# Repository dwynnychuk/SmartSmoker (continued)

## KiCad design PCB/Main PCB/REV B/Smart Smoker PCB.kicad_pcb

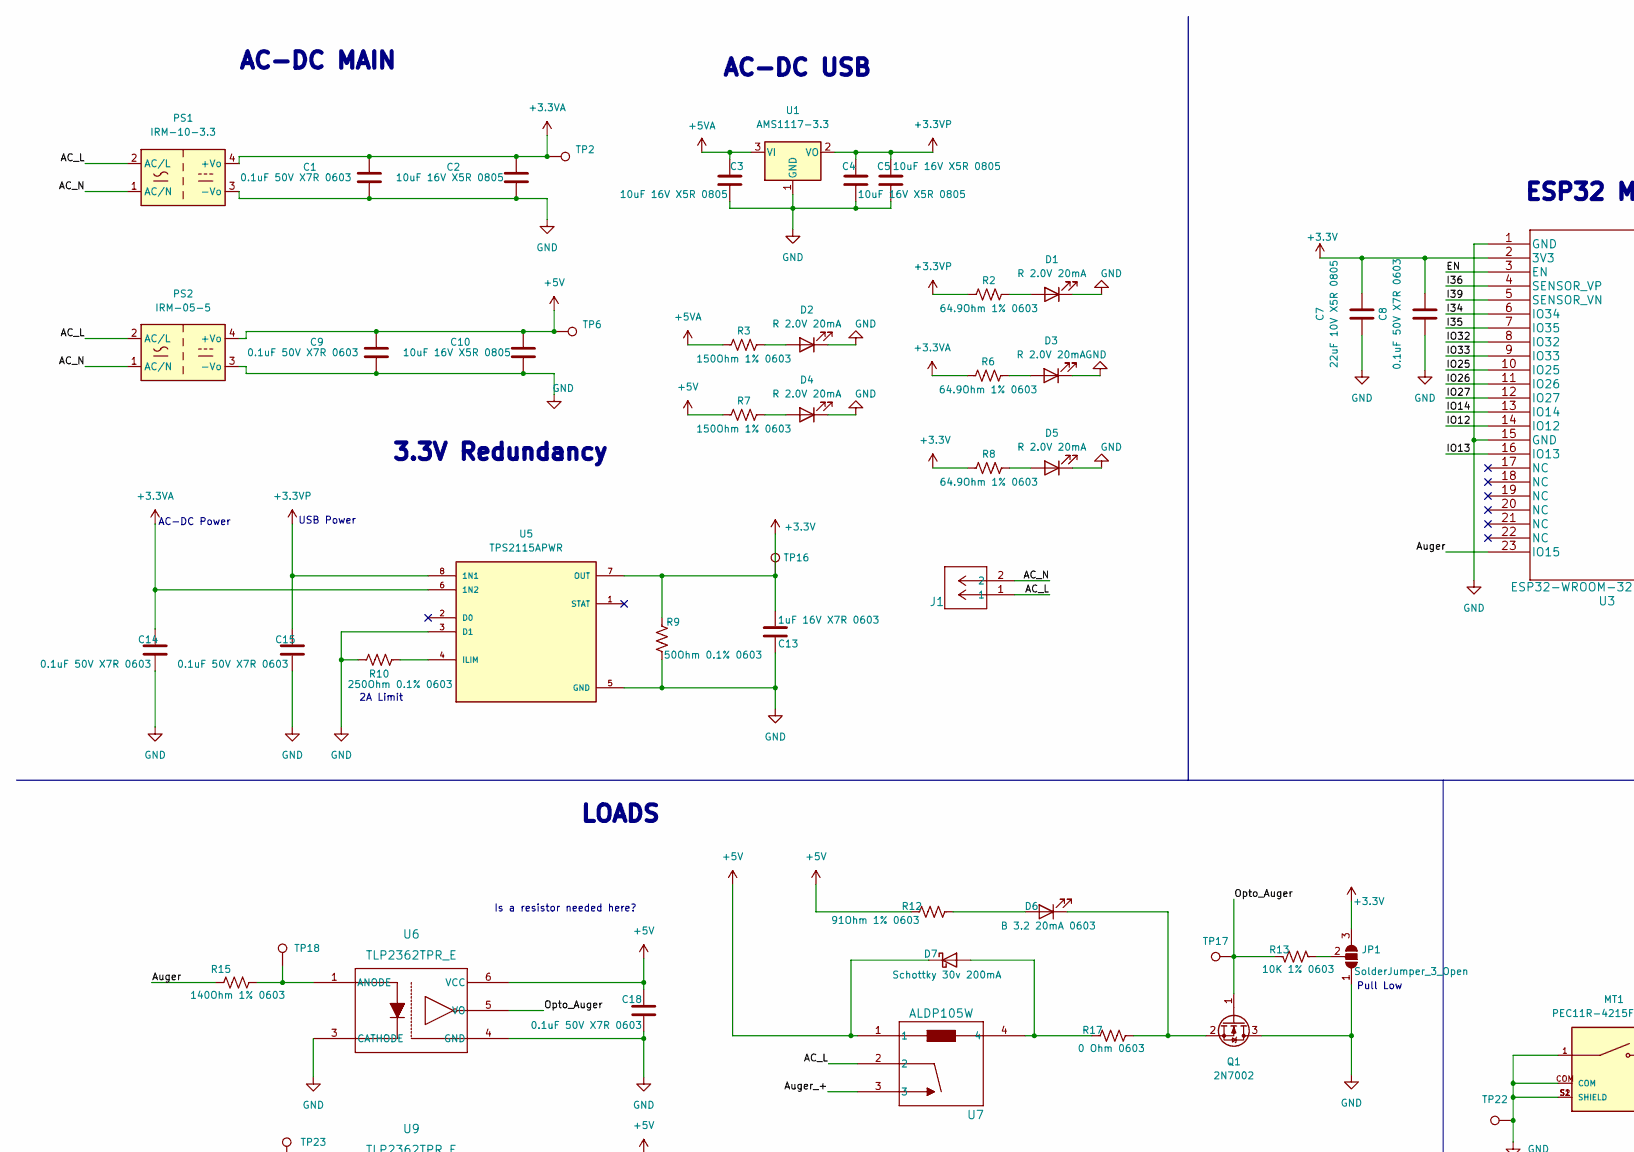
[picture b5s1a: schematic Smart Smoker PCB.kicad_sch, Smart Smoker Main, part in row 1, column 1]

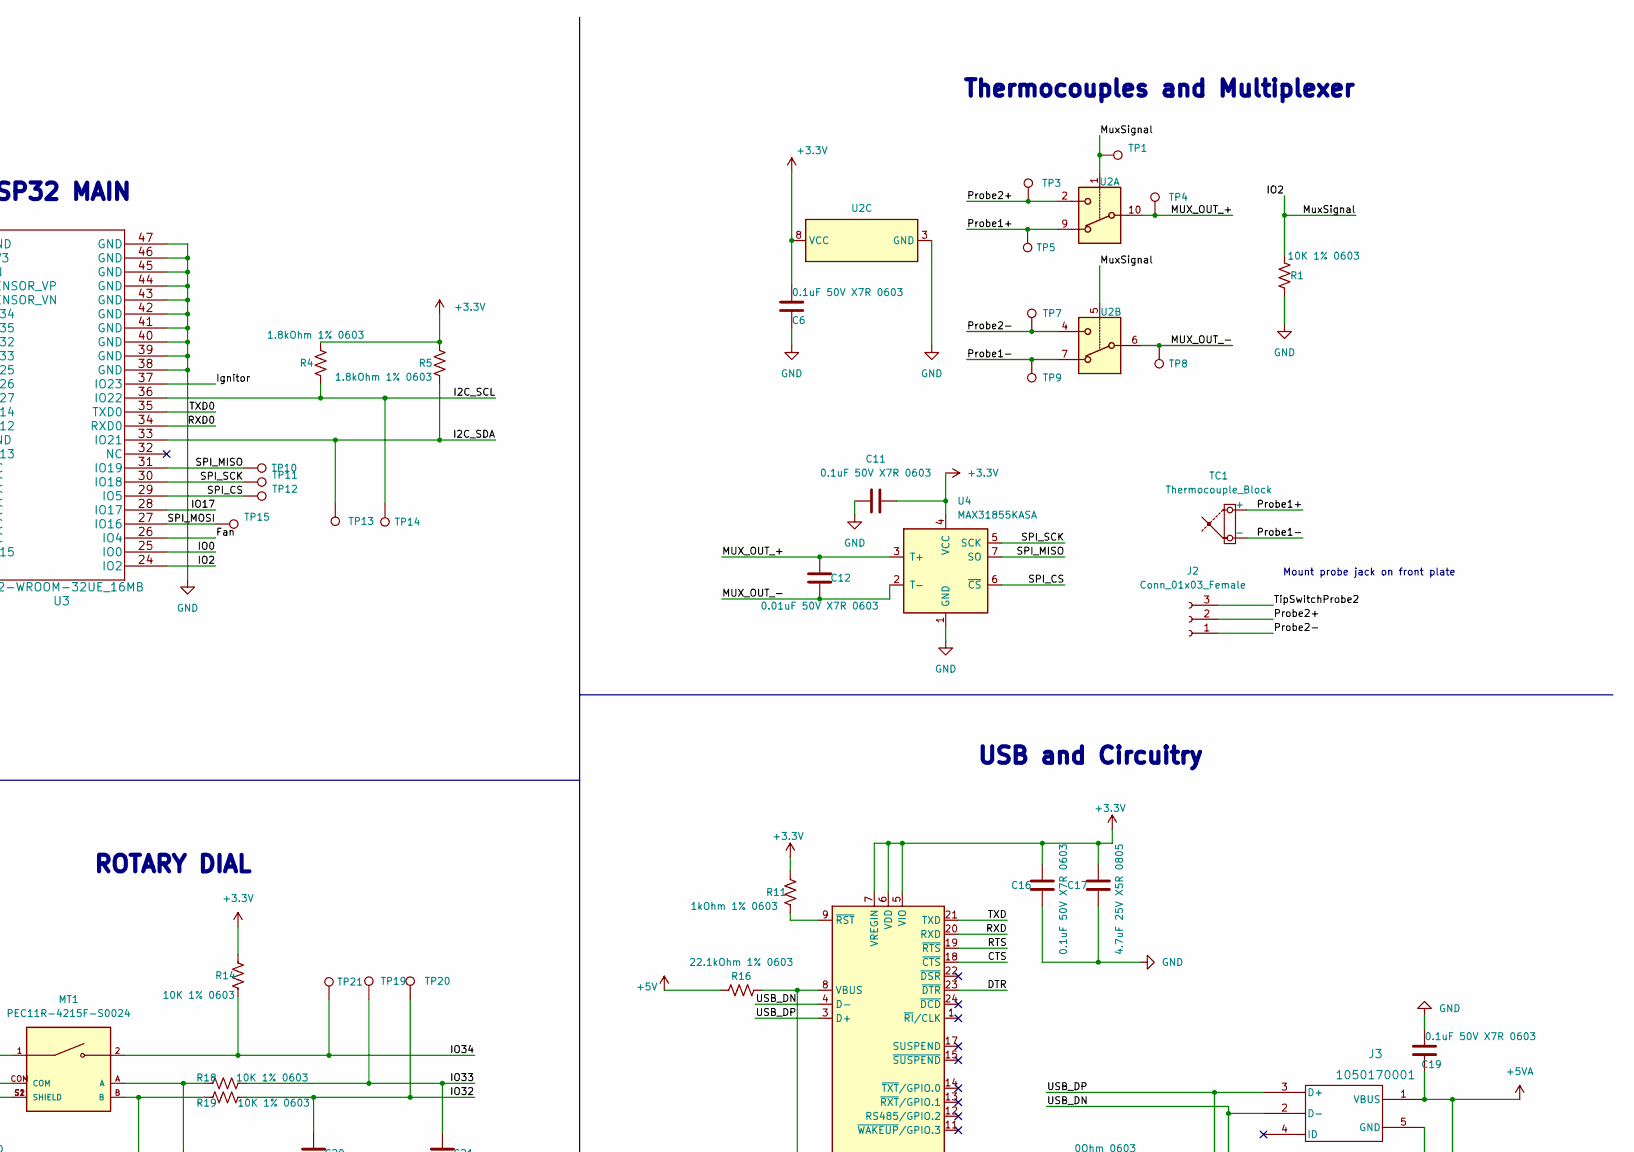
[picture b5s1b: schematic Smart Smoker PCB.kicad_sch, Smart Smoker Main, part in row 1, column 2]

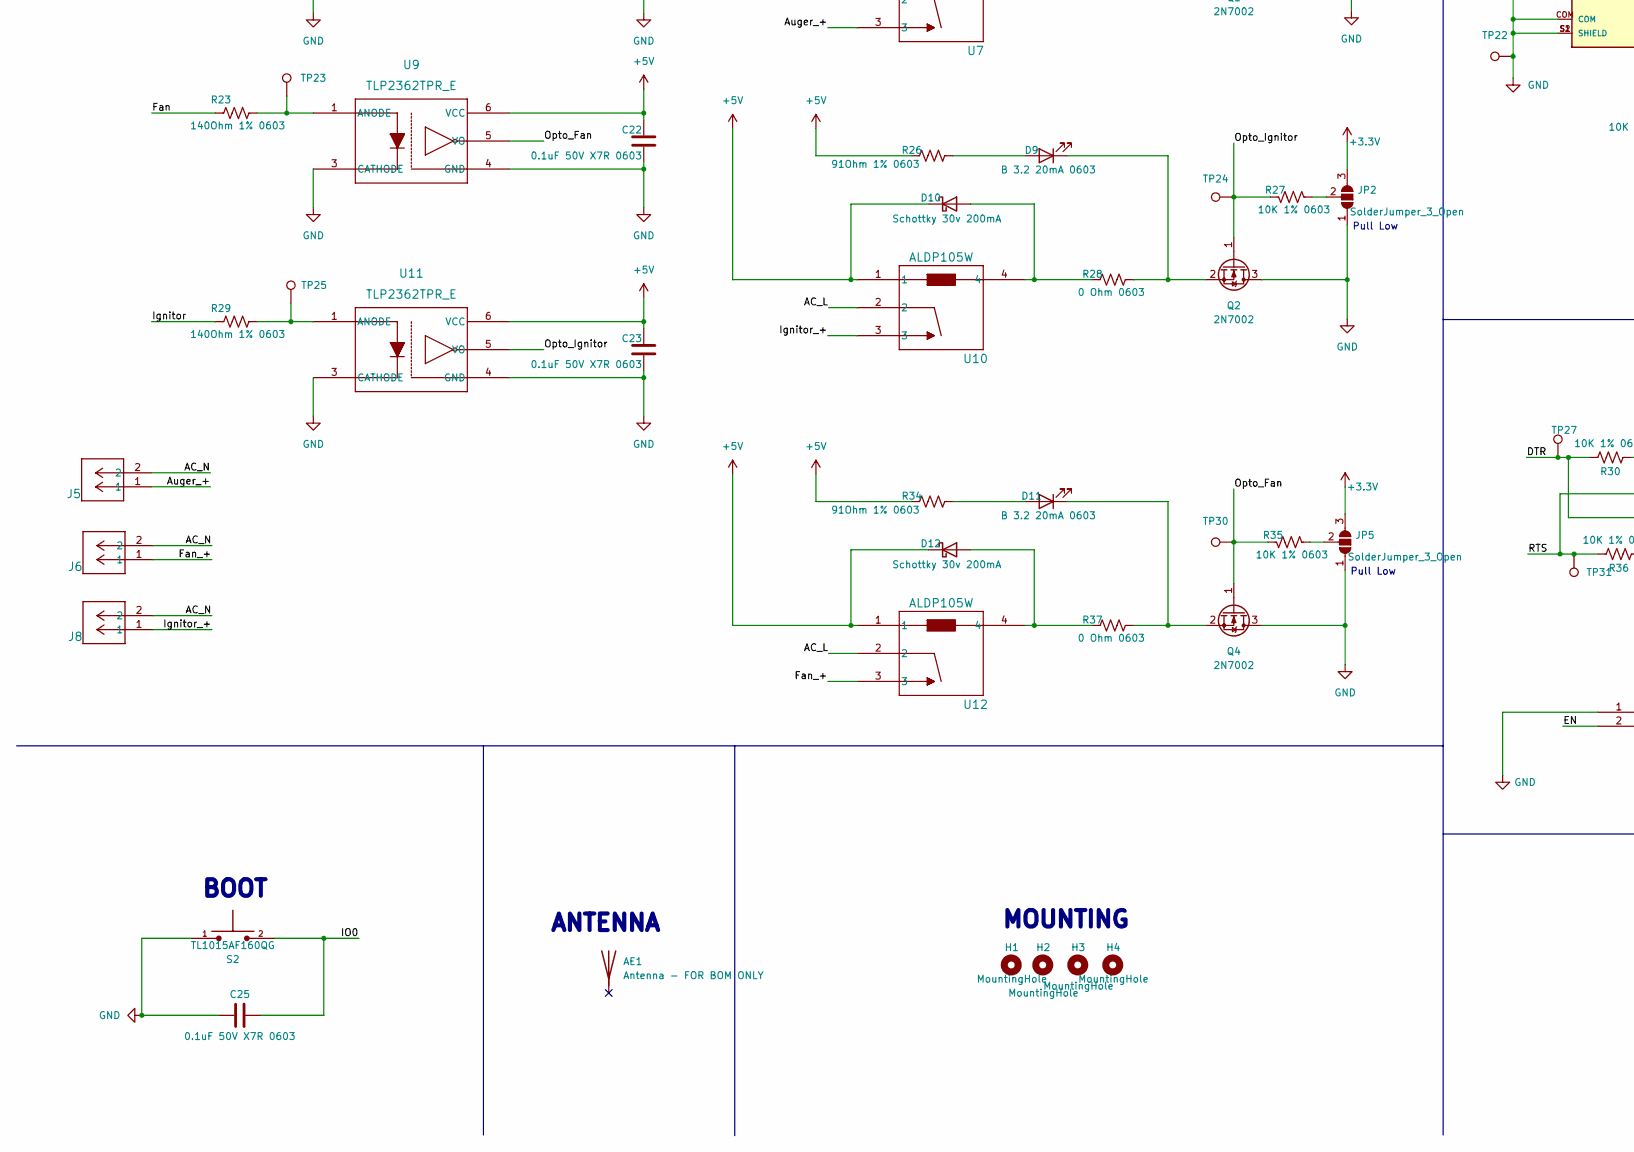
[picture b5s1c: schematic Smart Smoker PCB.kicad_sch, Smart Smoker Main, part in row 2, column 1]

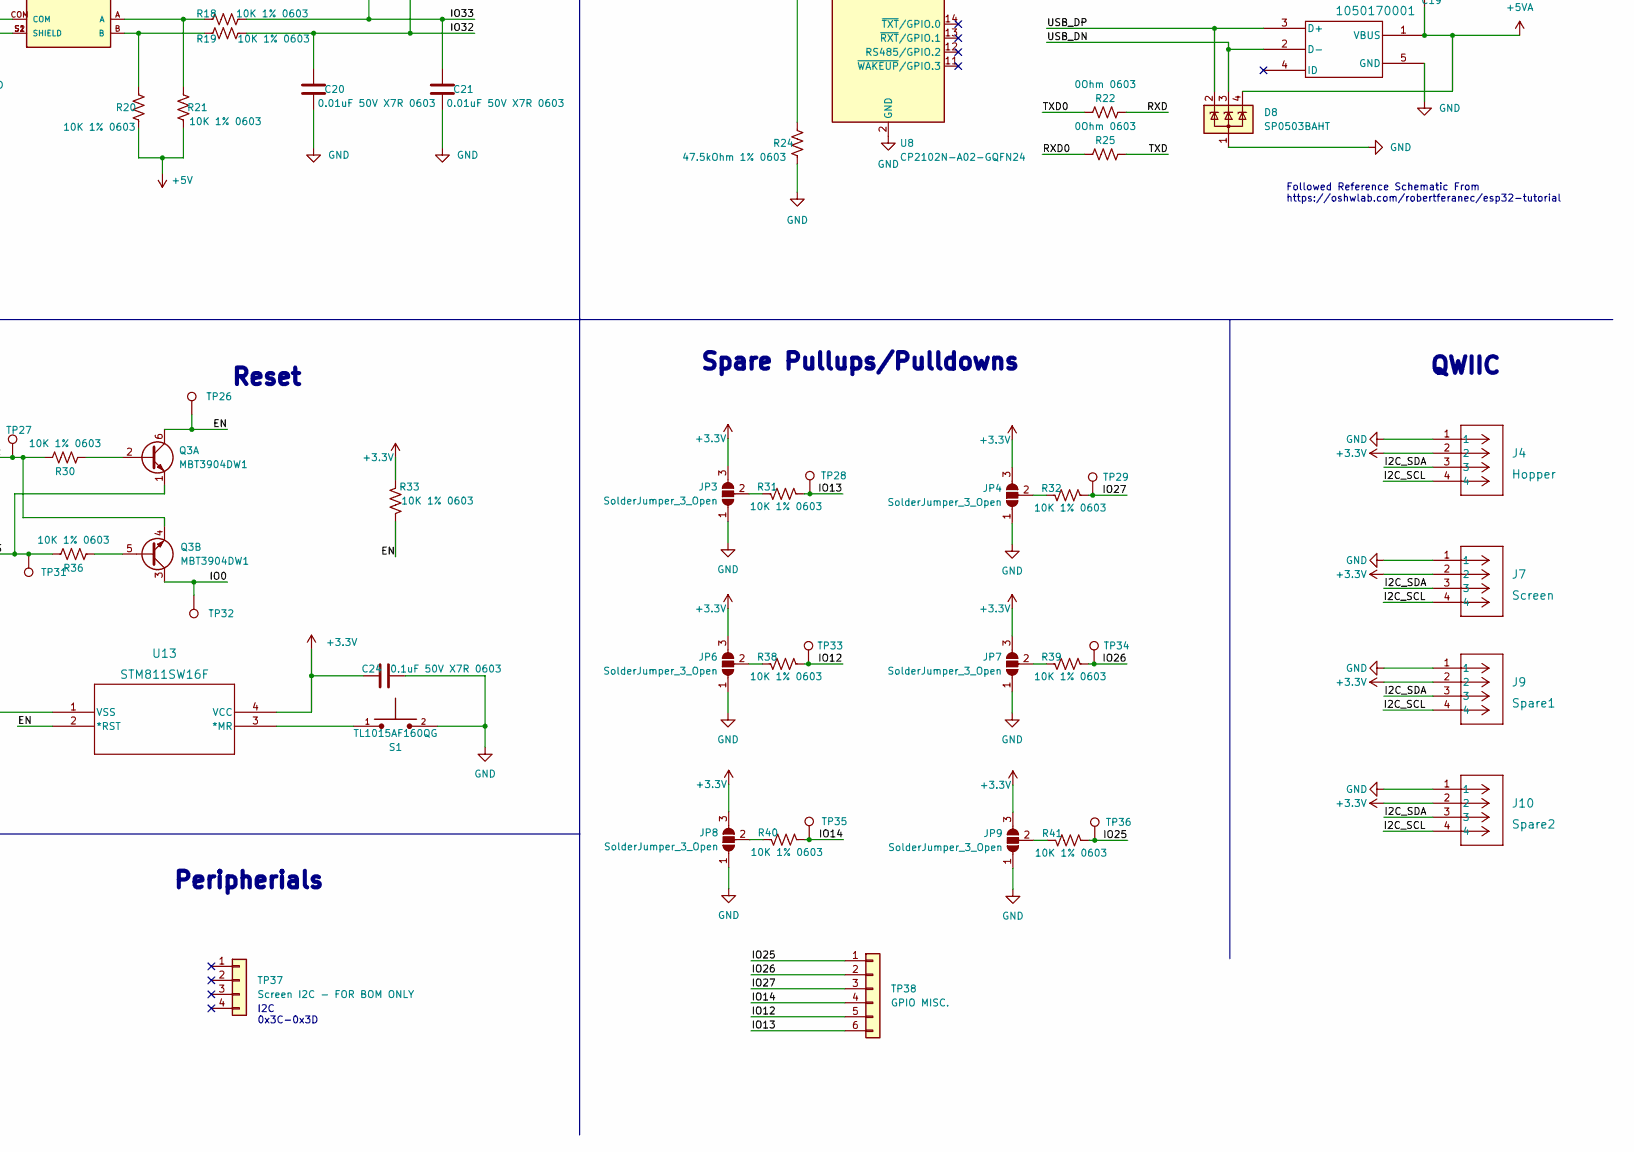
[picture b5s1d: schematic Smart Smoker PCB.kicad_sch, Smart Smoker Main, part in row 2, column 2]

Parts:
AE1: Antenna - FOR BOM ONLY; KiCad-Logo2_5mm_SilkScreen; Manufacturer Part Number W3921B0100
C1, C6, C8, C9, C11, C14, C15, C16, C18, C19, C22, C23, C24, C25: 0.1uF 50V X7R 0603; C_0603_1608Metric; Manufacturer Part Number CL10B104KB8NNWC
C2, C3, C4, C5, C10: 10uF 16V X5R 0805; C_0805_2012Metric; Manufacturer Part Number CL21A106KOQNNNE
C7: 22uF 10V X5R 0805; C_0805_2012Metric; Manufacturer Part Number CL21A226MPQNNNE
C12, C20, C21: 0.01uF 50V X7R 0603; C_0603_1608Metric; Manufacturer Part Number CL10B103KB8NNNC
C13: 1uF 16V X7R 0603; C_0603_1608Metric; Manufacturer Part Number CC0603KRX7R7BB105
C17: 4.7uF 25V X5R 0805; C_0805_2012Metric; Manufacturer Part Number CL21A475KAQNNNE
D1, D2, D3, D4, D5: R 2.0V 20mA; LED_0603_1608Metric; Manufacturer Part Number LO Q976-PS-25-0-20-R18
D6, D9, D11: B 3.2 20mA 0603; LED_0603_1608Metric; Manufacturer Part Number 150060BS75000
D7, D10, D12: Schottky 30v 200mA; RB521S30T1G-M; Manufacturer Part Number RB521S30T1G
D8: SP0503BAHT; SOT-143; Manufacturer Part Number SP0503BAHTG
H1, H2, H3, H4: MountingHole; MountingHole_3.2mm_M3_DIN965_Pad
J1, J5, J6, J8: 393570002; CONN_393570002_MOL; Manufacturer Part Number 393570002
J2: Conn_01x03_Female; PinHeader_1x03_P2.54mm_Vertical; Manufacturer Part Number MJ-3502
J3: 1050170001; USB_Micro-B_Molex-105017-0001; Manufacturer Part Number 1050170001
J4: Hopper; PRT-14417; Manufacturer Part Number PRT-14417
J7: Screen; PRT-14417; Manufacturer Part Number PRT-14417
J9: Spare1; PRT-14417; Manufacturer Part Number PRT-14417
J10: Spare2; PRT-14417; Manufacturer Part Number PRT-14417
JP1, JP2, JP3, JP4, JP5, JP6, JP7, JP8, JP9: SolderJumper_3_Open; SolderJumper-3_P1.3mm_Open_RoundedPad1.0x1.5mm
MT1: PEC11R-4215F-S0024; XDCR_PEC11R-4215F-S0024; Manufacturer Part Number PEC11R-4220K-S0024
PS1: IRM-10-3.3; Converter_ACDC_MeanWell_IRM-10-xx_THT; Manufacturer Part Number IRM-10-3.3
PS2: IRM-05-5; Converter_ACDC_MeanWell_IRM-05-xx_THT
Q1, Q2, Q4: 2N7002; SOT-23; Manufacturer Part Number 1727-4789-1-ND
Q3: MBT3904DW1; SOT-363_SC-70-6
R1, R13, R14, R18, R19, R20, R21, R27, R30, R31, R32, R33, R35, R36, R38, R39, R40, R41: 10K 1% 0603; R_0603_1608Metric; Manufacturer Part Number RNCP0603FTD10K0
R2, R6, R8: 64.9Ohm 1% 0603; R_0603_1608Metric; Manufacturer Part Number RC0603FR-0764R9L
R3, R7: 150Ohm 1% 0603; R_0603_1608Metric; Manufacturer Part Number RC0603FR-07150RL
R4, R5: 1.8kOhm 1% 0603; R_0603_1608Metric; Manufacturer Part Number CRGCQ0603F1K8
R9: 50Ohm 0.1% 0603; R_0603_1608Metric; Manufacturer Part Number RT0603BRE0750RL
R10: 250Ohm 0.1% 0603; R_0603_1608Metric; Manufacturer Part Number RT0603BRE07250RL
R11: 1kOhm 1% 0603; R_0603_1608Metric; Manufacturer Part Number RNCP0603FTD1K00
R12, R26, R34: 91Ohm 1% 0603; R_0603_1608Metric; Manufacturer Part Number RC0603FR-0791RL
R15, R23, R29: 140Ohm 1% 0603; R_0603_1608Metric; Manufacturer Part Number RC0603FR-07140RL
R16: 22.1kOhm 1% 0603; R_0603_1608Metric; Manufacturer Part Number RC0603FR-0722K1L
R17, R28, R37: 0 Ohm 0603; R_0603_1608Metric; Manufacturer Part Number RC0603JR-070RL
R22, R25: 0Ohm 0603; R_0603_1608Metric; Manufacturer Part Number RMCF0603ZT0R00
R24: 47.5kOhm 1% 0603; R_0603_1608Metric; Manufacturer Part Number RC0603FR-0747K5L
S1, S2: TL1015AF160QG; SW_TL1015AF160QG; PARTREV F
TC1: Thermocouple_Block; K-TypeAdapter; Manufacturer Part Number XE-1139-001
TP1, TP2, TP3, TP4, TP5, TP6, TP7, TP8, TP9, TP10, TP11, TP12, TP13, TP14, TP15, TP16, TP17, TP18, TP19, TP20, TP21, TP22, TP23, TP24, TP25, TP26, TP27, TP28, TP29, TP30, TP31, TP32, TP33, TP34, TP35, TP36: TP; TestPoint_Pad_D1.0mm
TP37: Screen I2C - FOR BOM ONLY; PinHeader_1x04_P2.54mm_Vertical; Manufacturer Part Number 938
TP38: GPIO MISC.; PinHeader_1x06_P2.54mm_Vertical
U1: AMS1117-3.3; TO-252-2; Manufacturer Part Number AMS1117CD-3.3
U2: TS5A23159DGS; VSSOP-10_3x3mm_P0.5mm; Manufacturer Part Number TS5A23159DGSR
U3: ESP32-WROOM-32UE_16MB; ESP32-WROOM-32UE 16MB; Manufacturer Part Number ESP32-WROOM-32UE-N4
U4: MAX31855KASA; SOIC-8_3.9x4.9mm_P1.27mm; Manufacturer Part Number MAX31855KASA+T
U5: TPS2115APWR; PW8-M; Manufacturer Part Number TPS2115APWR
U6, U9, U11: TLP2362TPR_E; TLP2362; Manufacturer Part Number TLP2362(TPR,E
U7, U10, U12: ALDP105W; PAN_ALD_PAN; Manufacturer Part Number ALDP105W
U8: CP2102N-A02-GQFN24; QFN-24-1EP_4x4mm_P0.5mm_EP2.6x2.6mm; Manufacturer Part Number CP2102N-A02-GQFN24
U13: STM811SW16F; Manufacturer Part Number STM811SW16F

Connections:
+3.3V: C6.2, C7.2, C8.2, C11.1, C13.1, C16.2, C17.2, C24.2, J4.2, J7.2, J9.2, J10.2, JP1.3 (B), JP2.3 (B), JP3.3 (B), JP4.3 (B), JP5.3 (B), JP6.3 (B), JP7.3 (B), JP8.3 (B), JP9.3 (B), R4.2, R5.2, R8.1, R9.2, R11.2, R14.2, R33.2, TP16.1, U2.8 (VCC), U3.2 (3V3), U4.4 (VCC), U5.7 (OUT), U8.5 (VIO), U8.6 (VDD), U8.7 (VREGIN), U13.4 (VCC)
+3.3VA: C1.2, C2.1, C14.2, PS1.4 (+Vo), R6.1, TP2.1, U5.6 (1N2)
+3.3VP: C4.1, C5.1, C15.2, R2.1, U1.2 (VO), U5.8 (1N1)
+5V: C9.2, C10.1, C18.1, C22.1, C23.1, D7.1 (K), D10.1 (K), D12.1 (K), PS2.4 (+Vo), R7.1, R12.1, R16.1, R20.1, R21.1, R26.1, R34.1, TP6.1, U6.6 (VCC), U7.1, U9.6 (VCC), U10.1, U11.6 (VCC), U12.1
+5VA: C3.1, C19.1, D8.4 (K), J3.1 (VBUS), R3.1, U1.3 (VI)
/AC_L: J1.1, PS1.2 (AC/L), PS2.2 (AC/L), U7.2, U10.2, U12.2
/AC_N: J1.2, J5.2, J6.2, J8.2, PS1.1 (AC/N), PS2.1 (AC/N)
/Auger: R15.1, U3.23 (IO15)
/Auger_+: J5.1, U7.3
/CTS: U8.18 (~CTS)
/DTR: Q3.4 (E2), R30.1, TP27.1, U8.23 (~DTR)
/EN: Q3.6 (C1), R33.1, TP26.1, U3.3 (EN), U13.2 (*RST)
/Fan: R23.1, U3.26 (IO4)
/Fan_+: J6.1, U12.3
/I2C_SCL: J4.4, J7.4, J9.4, J10.4, R4.1, TP14.1, U3.36 (IO22)
/I2C_SDA: J4.3, J7.3, J9.3, J10.3, R5.1, TP13.1, U3.33 (IO21)
/I34: U3.6 (IO34)
/I35: U3.7 (IO35)
/I36: U3.4 (SENSOR_VP)
/I39: U3.5 (SENSOR_VN)
/IO0: C25.1, Q3.3 (C2), S2.2, TP32.1, U3.25 (IO0)
/IO2: R1.1, TP1.1, U2.1, U2.5, U3.24 (IO2)
/IO12: R38.1, TP33.1, TP38.5, U3.14 (IO12)
/IO13: R31.1, TP28.1, TP38.6, U3.16 (IO13)
/IO14: R40.1, TP35.1, TP38.4, U3.13 (IO14)
/IO17: U3.28 (IO17)
/IO25: R41.1, TP36.1, TP38.1, U3.10 (IO25)
/IO26: R39.1, TP34.1, TP38.2, U3.11 (IO26)
/IO27: R32.1, TP29.1, TP38.3, U3.12 (IO27)
/IO32: C20.1, R19.2, TP20.1, U3.8 (IO32)
/IO33: C21.1, R18.2, TP19.1, U3.9 (IO33)
/IO34: MT1.2, R14.1, TP21.1
/Ignitor: R29.1, U3.37 (IO23)
/Ignitor_+: J8.1, U10.3
/MUX_OUT_+: C12.1, TP4.1, U2.10, U4.3 (T+)
/MUX_OUT_-: C12.2, TP8.1, U2.6, U4.2 (T-)
/Opto_Auger: Q1.1 (G), R13.2, TP17.1, U6.5 (VO)
/Opto_Fan: Q4.1 (G), R35.2, TP30.1, U9.5 (VO)
/Opto_Ignitor: Q2.1 (G), R27.2, TP24.1, U11.5 (VO)
/Probe1+: TC1.1 (+), TP5.1, U2.9
/Probe1-: TC1.2 (-), TP9.1, U2.7
/Probe2+: J2.2, TP3.1, U2.2
/Probe2-: J2.1, TP7.1, U2.4
/RTS: Q3.1 (E1), R36.1, TP31.1, U8.19 (~RTS)
/RXD: R22.2, U8.20 (RXD)
/RXD0: R25.1, U3.34 (RXD0)
/SPI_CS: TP12.1, U3.29 (IO5), U4.6 (~CS)
/SPI_MISO: TP10.1, U3.31 (IO19), U4.7 (SO)
/SPI_MOSI: TP15.1, U3.27 (IO16)
/SPI_SCK: TP11.1, U3.30 (IO18), U4.5 (SCK)
/TXD: R25.2, U8.21 (TXD)
/TXD0: R22.1, U3.35 (TXD0)
/TipSwitchProbe2: J2.3
/USB_DN: D8.3 (K), J3.2 (D-), U8.4 (D-)
/USB_DP: D8.2 (K), J3.3 (D+), U8.3 (D+)
GND: C1.1, C2.2, C3.2, C4.2, C5.2, C6.1, C7.1, C8.1, C9.1, C10.2, C11.2, C13.2, C14.1, C15.1, C16.1, C17.1, C18.2, C19.2, C20.2, C21.2, C22.2, C23.2, C24.1, C25.2, D1.1 (K), D2.1 (K), D3.1 (K), D4.1 (K), D5.1 (K), D8.1 (A), J3.5 (GND), J4.1, J7.1, J9.1, J10.1, JP1.1 (A), JP2.1 (A), JP3.1 (A), JP4.1 (A), JP5.1 (A), JP6.1 (A), JP7.1 (A), JP8.1 (A), JP9.1 (A), MT1.1, MT1.COM, MT1.S1 (SHIELD), MT1.S2 (SHIELD), PS1.3 (-Vo), PS2.3 (-Vo), Q1.3 (D), Q2.3 (D), Q4.3 (D), R1.2, R9.1, R10.2, R24.1, S1.2, S2.1, TP22.1, U1.1 (GND), U2.3 (GND), U3.1 (GND), U3.15 (GND), U3.38 (GND), U3.39 (GND), U3.40 (GND), U3.41 (GND), U3.42 (GND), U3.43 (GND), U3.44 (GND), U3.45 (GND), U3.46 (GND), U3.47 (GND), U4.1 (GND), U5.3 (D1), U5.5 (GND), U6.3 (CATHODE), U6.4 (GND), U8.2 (GND), U8.25 (GND), U9.3 (CATHODE), U9.4 (GND), U11.3 (CATHODE), U11.4 (GND), U13.1 (VSS)
unnamed: D1.2 (A), R2.2
unnamed: D2.2 (A), R3.2
unnamed: D3.2 (A), R6.2
unnamed: D4.2 (A), R7.2
unnamed: D5.2 (A), R8.2
unnamed: D6.1 (K), Q1.2 (S), R17.2
unnamed: D6.2 (A), R12.2
unnamed: D7.2 (A), R17.1, U7.4
unnamed: D9.1 (K), Q2.2 (S), R28.2
unnamed: D9.2 (A), R26.2
unnamed: D10.2 (A), R28.1, U10.4
unnamed: D11.1 (K), Q4.2 (S), R37.2
unnamed: D11.2 (A), R34.2
unnamed: D12.2 (A), R37.1, U12.4
unnamed: JP1.2 (C), R13.1
unnamed: JP2.2 (C), R27.1
unnamed: JP3.2 (C), R31.2
unnamed: JP4.2 (C), R32.2
unnamed: JP5.2 (C), R35.1
unnamed: JP6.2 (C), R38.2
unnamed: JP7.2 (C), R39.2
unnamed: JP8.2 (C), R40.2
unnamed: JP9.2 (C), R41.2
unnamed: MT1.A, R18.1, R21.2
unnamed: MT1.B, R19.1, R20.2
unnamed: Q3.2 (B1), R30.2
unnamed: Q3.5 (B2), R36.2
unnamed: R10.1, U5.4 (ILIM)
unnamed: R11.1, U8.9 (~RST)
unnamed: R15.2, TP18.1, U6.1 (ANODE)
unnamed: R16.2, R24.2, U8.8 (VBUS)
unnamed: R23.2, TP23.1, U9.1 (ANODE)
unnamed: R29.2, TP25.1, U11.1 (ANODE)
unnamed: S1.1, U13.3 (*MR)

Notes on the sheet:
Peripherials
MOUNTING
Reset
2A Limit
Pull Low
AC-DC USB
BOOT
USB and Circuitry
USB Power
Is a resistor needed here?
LOADS
I2C 0x3C-0x3D
Spare Pullups/Pulldowns
Thermocouples and Multiplexer
Mount probe jack on front plate
Followed Reference Schematic From https://oshwlab.com/robertferanec/esp32-tutorial
QWIIC
AC-DC Power
ANTENNA
ESP32 MAIN
ROTARY DIAL
3.3V Redundancy
AC-DC MAIN

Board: 4 copper layers, 161 parts (0 on the bottom side), 83 nets, no tracks yet.

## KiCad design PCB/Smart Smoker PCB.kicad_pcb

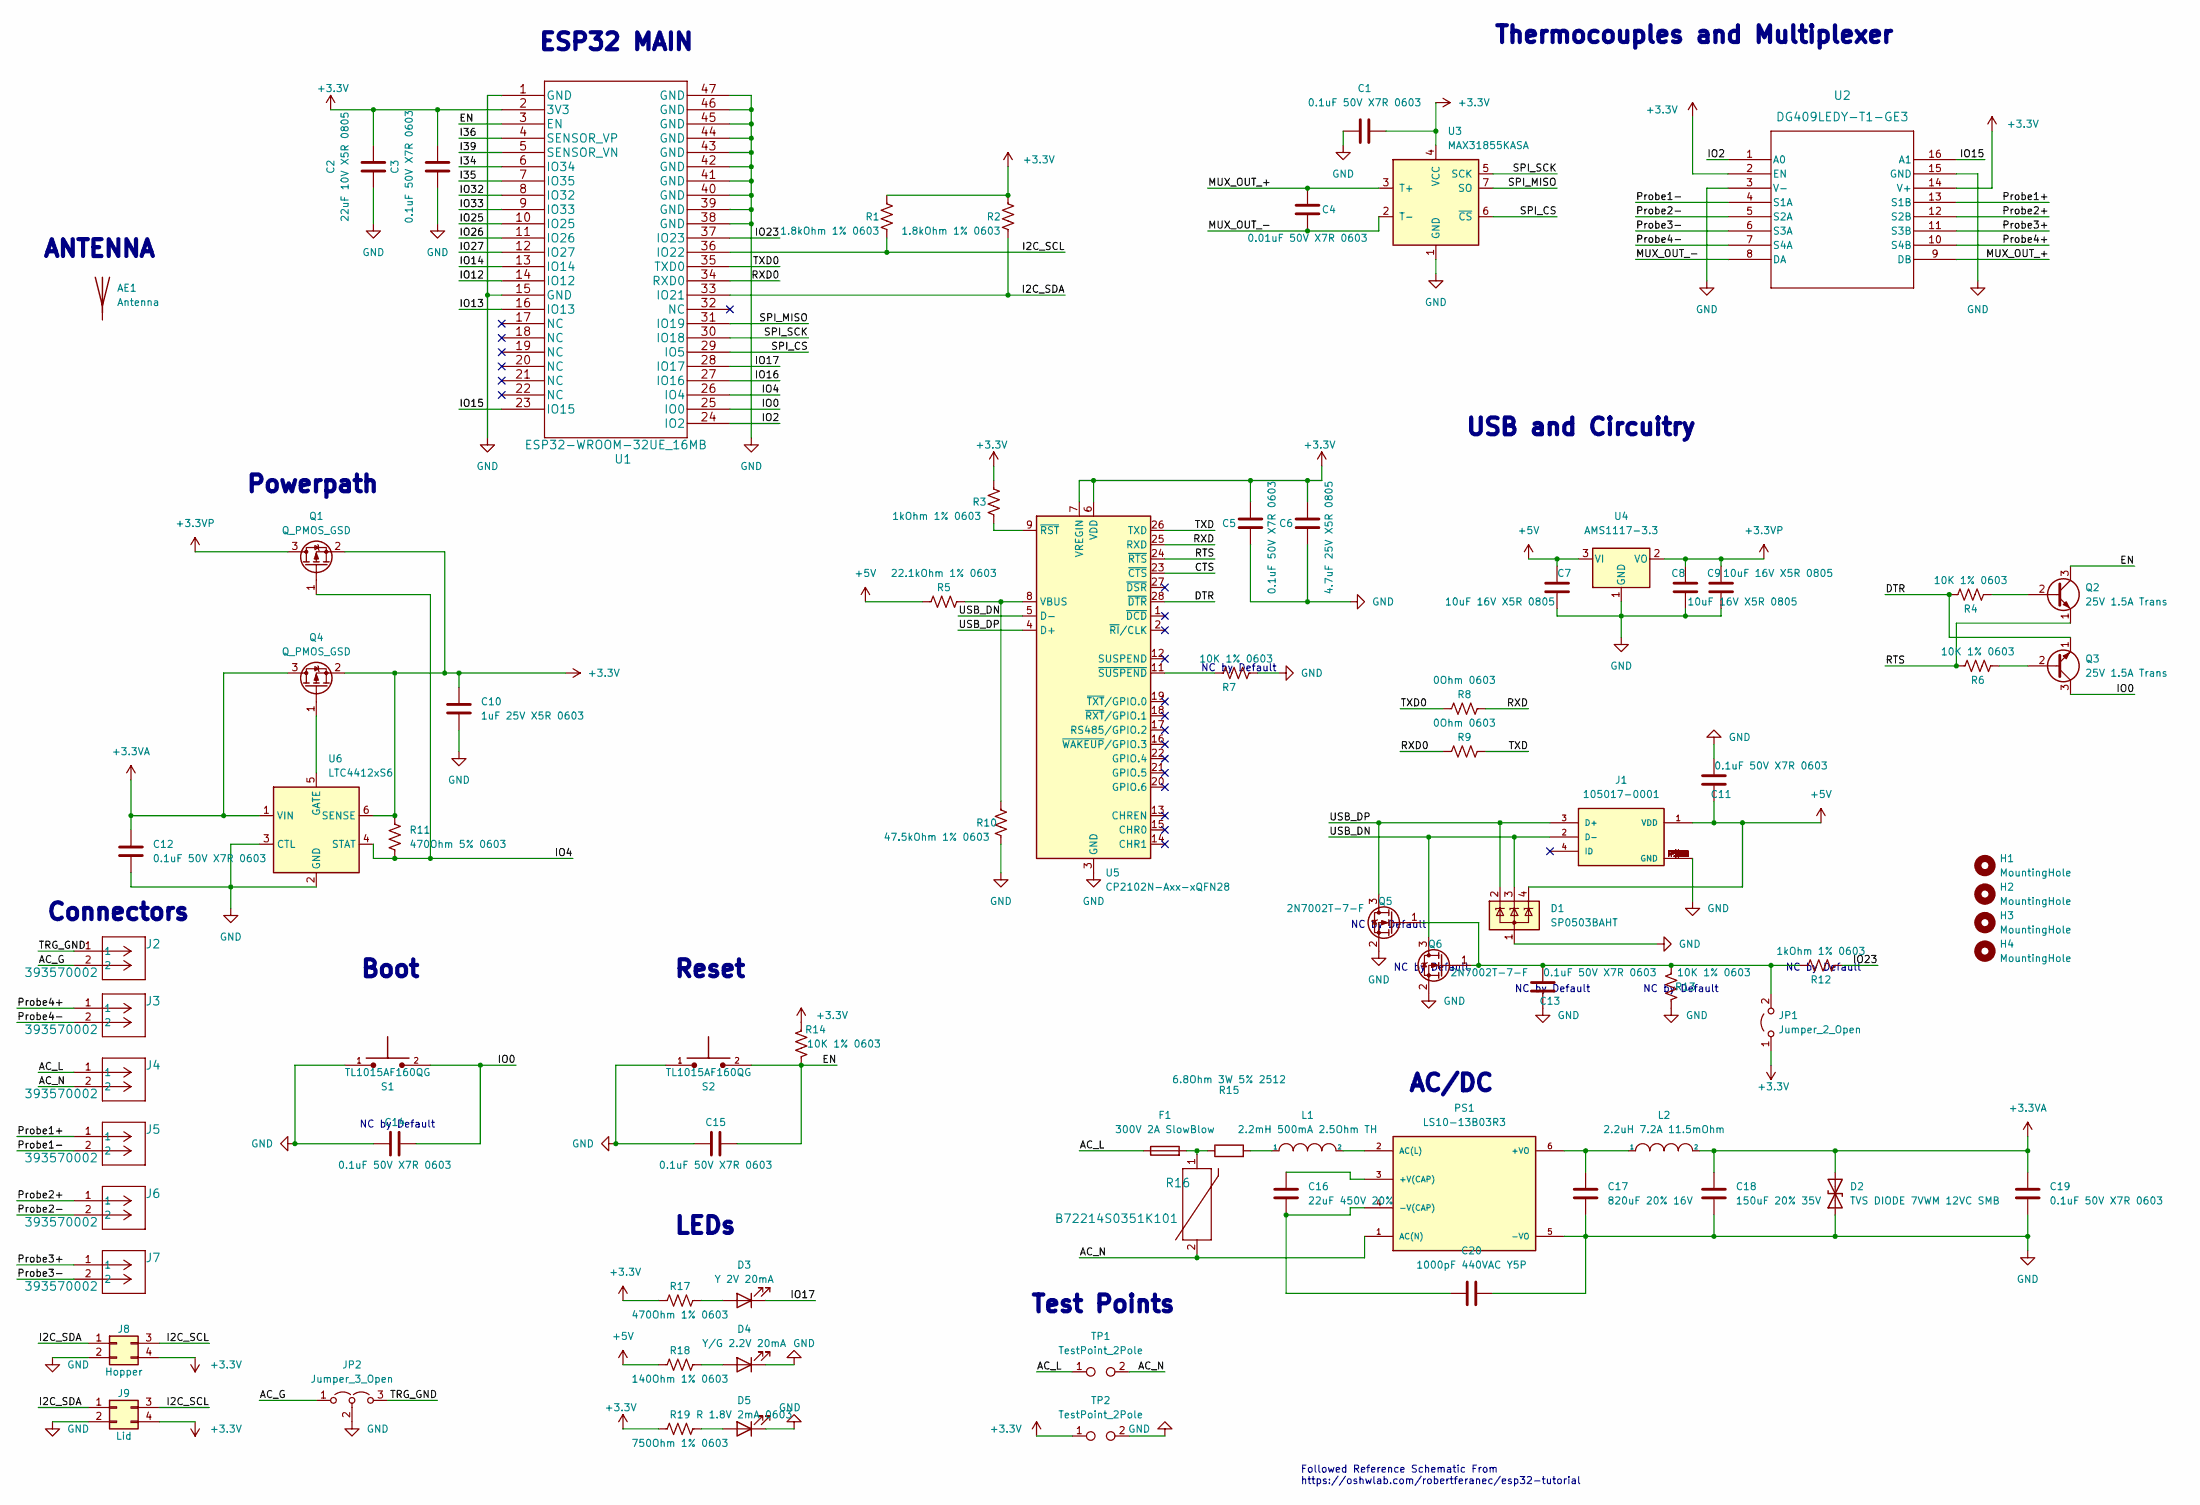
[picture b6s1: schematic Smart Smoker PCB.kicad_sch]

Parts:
AE1: Antenna; KiCad-Logo2_5mm_SilkScreen; Manufacturer Part Number W3921B0100
C1, C3, C5, C11, C12, C13, C14, C15, C19: 0.1uF 50V X7R 0603; C_0603_1608Metric; Manufacturer Part Number CL10B104KB8NNWC
C2: 22uF 10V X5R 0805; C_0805_2012Metric; Manufacturer Part Number CL21A226MPQNNNE
C4: 0.01uF 50V X7R 0603; C_0603_1608Metric; Manufacturer Part Number CL10B103KB8NNNC
C6: 4.7uF 25V X5R 0805; C_0805_2012Metric; Manufacturer Part Number CL21A475KAQNNNE
C7, C8, C9: 10uF 16V X5R 0805; C_0805_2012Metric; Manufacturer Part Number CL21A106KOQNNNE
C10: 1uF 25V X5R 0603; C_0603_1608Metric; Manufacturer Part Number CL10A105KA8NNNC
C16: 22uF 450V 20%; CP_Radial_D12.5mm_P5.00mm; Manufacturer Part Number UCY2W220MHD
C17: 820uF 20% 16V; CP_Radial_D10.0mm_P5.00mm; Manufacturer Part Number 860010375016
C18: 150uF 20% 35V; CP_Radial_D8.0mm_P3.50mm; Manufacturer Part Number 860020574010
C20: 1000pF 440VAC Y5P; C_Disc_D9.0mm_W5.0mm_P7.50mm; Manufacturer Part Number C927U102KZYDAA7317
D1: SP0503BAHT; SOT-143; Manufacturer Part Number SP0503BAHTG
D2: TVS DIODE 7VWM 12VC SMB; D_SMB; Manufacturer Part Number SMBJ7.0A
D3: Y 2V 20mA; LED_0603_1608Metric; Manufacturer Part Number 150060YS75000
D4: Y/G 2.2V 20mA; LED_0603_1608Metric; Manufacturer Part Number BL-HGE36D-AV-TRB
D5: R 1.8V 2mA 0603; LED_0603_1608Metric; Manufacturer Part Number CSL1901UW1
F1: 300V 2A SlowBlow; Fuse_Littelfuse_395Series; Manufacturer Part Number 36912000000
H1, H2, H3, H4: MountingHole; MountingHole_3.2mm_M3_DIN965_Pad
J1: 105017-0001; MOLEX_105017-0001; Manufacturer Part Number 1050170001
J2, J3, J4, J5, J6, J7: 393570002; CONN_393570002_MOL; Manufacturer Part Number 393570002
J8: Hopper; Molex_Micro-Fit_3.0_43045-0400_2x02_P3.00mm_Horizontal; Manufacturer Part Number 0430450400
J9: Lid; Molex_Micro-Fit_3.0_43045-0400_2x02_P3.00mm_Horizontal; Manufacturer Part Number 0430450400
JP1: Jumper_2_Open; PinHeader_1x02_P2.54mm_Vertical
JP2: Jumper_3_Open; SolderJumper-3_P1.3mm_Open_RoundedPad1.0x1.5mm
L1: 2.2mH 500mA 2.5Ohm TH; L_Radial_D10.5mm_P5.00mm_Abacron_AISR-01; Manufacturer Part Number 7687480222
L2: 2.2uH 7.2A 11.5mOhm; L_Taiyo-Yuden_NR-80xx; Manufacturer Part Number BWVS008080402R2M00
PS1: LS10-13B03R3; CONV_LS10-13B03R3; PARTREV 2020.12.14-A/5
Q1, Q4: Q_PMOS_GSD; VESM_TOS; Manufacturer Part Number SSM3J56MFV,L3F
Q2, Q3: 25V 1.5A Trans; SOT-23-3; Manufacturer Part Number SS8050-G
Q5, Q6: 2N7002T-7-F; SOT-23; Manufacturer Part Number 2N7002T-7-F
R1, R2: 1.8kOhm 1% 0603; R_0603_1608Metric; Manufacturer Part Number CRGCQ0603F1K8
R3, R12: 1kOhm 1% 0603; R_0603_1608Metric; Manufacturer Part Number RNCP0603FTD1K00
R4, R6, R7, R13, R14: 10K 1% 0603; R_0603_1608Metric; Manufacturer Part Number RNCP0603FTD10K0
R5: 22.1kOhm 1% 0603; R_0603_1608Metric; Manufacturer Part Number RC0603FR-0722K1L
R8, R9: 0Ohm 0603; R_0603_1608Metric; Manufacturer Part Number RMCF0603ZT0R00
R10: 47.5kOhm 1% 0603; R_0603_1608Metric; Manufacturer Part Number RC0603FR-0747K5L
R11: 470Ohm 5% 0603; R_0603_1608Metric; Manufacturer Part Number RC0603JR-07470RL
R15: 6.8Ohm 3W 5% 2512; R_Box_L8.4mm_W2.5mm_P5.08mm; Manufacturer Part Number AC03000006808JAC00
R16: B72214S0351K101; VARS_B72214S_15P5X5P6-7P5-2P2_TDK; Manufacturer Part Number B72214S0351K101
R17: 470Ohm 1% 0603; R_0603_1608Metric; Manufacturer Part Number RC0603FR-13470RL
R18: 140Ohm 1% 0603; R_0603_1608Metric; Manufacturer Part Number RC0603FR-07140RL
R19: 750Ohm 1% 0603; R_0603_1608Metric; Manufacturer Part Number RC0603FR-07750RL
S1, S2: TL1015AF160QG; SW_TL1015AF160QG; PARTREV F
TP1, TP2: TestPoint_2Pole; TestPoint_2Pads_Pitch5.08mm_Drill1.3mm
U1: ESP32-WROOM-32UE_16MB; ESP32-WROOM-32UE 16MB; Manufacturer Part Number ESP32-WROOM-32UE-N4
U2: DG409LEDY-T1-GE3; SOIC16_NARROW_VIS; Manufacturer Part Number DG409LEDY-T1-GE3
U3: MAX31855KASA; SOIC-8_3.9x4.9mm_P1.27mm; Manufacturer Part Number MAX31855KASA+T
U4: AMS1117-3.3; SOT-223-3_TabPin2; Manufacturer Part Number AMS1117CD-3.3
U5: CP2102N-Axx-xQFN28; QFN-28-1EP_5x5mm_P0.5mm_EP3.35x3.35mm
U6: LTC4412xS6; TSOT-23-6; Manufacturer Part Number LTC4412ES6#TRMPBF

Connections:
+3.3V: C1.1, C2.2, C3.2, C5.2, C6.2, C10.2, J8.4, J9.4, JP1.1 (A), Q1.2 (S), Q4.2 (S), R1.2, R2.2, R3.2, R11.2, R14.2, R17.1, R19.1, TP2.1, U1.2 (3V3), U2.2 (EN), U2.14 (V+), U3.4 (VCC), U5.6 (VDD), U5.7 (VREGIN), U6.6 (SENSE)
+3.3VA: C12.1, C18.1, C19.1, D2.2 (A2), L2.2, Q4.3 (D), U6.1 (VIN)
+3.3VP: C8.1, C9.1, Q1.3 (D), U4.2 (VO)
+5V: C7.1, C11.1, D1.4 (K), J1.1 (VDD), R5.1, R18.1, U4.3 (VI)
/AC_G: J2.2, JP2.1 (A)
/AC_L: F1.1, J4.1, TP1.1
/AC_N: J4.2, PS1.1 (AC(N)), R16.2, TP1.2
/CTS: U5.23 (~CTS)
/DTR: Q3.1 (E), R4.1, U5.28 (~DTR)
/EN: C15.1, Q2.3 (C), R14.1, S2.2, U1.3 (EN)
/I2C_SCL: J8.3, J9.3, R1.1, U1.36 (IO22)
/I2C_SDA: J8.1, J9.1, R2.1, U1.33 (IO21)
/I34: U1.6 (IO34)
/I35: U1.7 (IO35)
/I36: U1.4 (SENSOR_VP)
/I39: U1.5 (SENSOR_VN)
/IO0: C14.2, Q3.3 (C), S1.2, U1.25 (IO0)
/IO2: U1.24 (IO2), U2.1 (A0)
/IO4: Q1.1 (G), R11.1, U1.26 (IO4), U6.4 (STAT)
/IO12: U1.14 (IO12)
/IO13: U1.16 (IO13)
/IO14: U1.13 (IO14)
/IO15: U1.23 (IO15), U2.16 (A1)
/IO16: U1.27 (IO16)
/IO17: D3.1 (K), U1.28 (IO17)
/IO23: R12.1, U1.37 (IO23)
/IO25: U1.10 (IO25)
/IO26: U1.11 (IO26)
/IO27: U1.12 (IO27)
/IO32: U1.8 (IO32)
/IO33: U1.9 (IO33)
/MUX_OUT_+: C4.1, U2.9 (DB), U3.3 (T+)
/MUX_OUT_-: C4.2, U2.8 (DA), U3.2 (T-)
/Probe1+: J5.1, U2.13 (S1B)
/Probe1-: J5.2, U2.4 (S1A)
/Probe2+: J6.1, U2.12 (S2B)
/Probe2-: J6.2, U2.5 (S2A)
/Probe3+: J7.1, U2.11 (S3B)
/Probe3-: J7.2, U2.6 (S3A)
/Probe4+: J3.1, U2.10 (S4B)
/Probe4-: J3.2, U2.7 (S4A)
/RTS: Q2.1 (E), R6.1, U5.24 (~RTS)
/RXD: R8.2, U5.25 (RXD)
/RXD0: R9.1, U1.34 (RXD0)
/SPI_CS: U1.29 (IO5), U3.6 (~CS)
/SPI_MISO: U1.31 (IO19), U3.7 (SO)
/SPI_SCK: U1.30 (IO18), U3.5 (SCK)
/TRG_GND: J2.1, JP2.3 (B)
/TXD: R9.2, U5.26 (TXD)
/TXD0: R8.1, U1.35 (TXD0)
/USB_DN: D1.3 (K), J1.2 (D-), Q6.3 (D), U5.5 (D-)
/USB_DP: D1.2 (K), J1.3 (D+), Q5.3 (D), U5.4 (D+)
GND: C1.2, C2.1, C3.1, C5.1, C6.1, C7.2, C8.2, C9.2, C10.1, C11.2, C12.2, C13.1, C14.1, C15.2, C17.2, C18.2, C19.2, C20.2, D1.1 (A), D2.1 (A1), D4.1 (K), D5.1 (K), J1.5 (GND), J1.P$1 (GND), J1.P$2 (GND), J1.P$8 (GND), J1.P$9 (GND), J1.P$10 (GND), J1.P$11 (GND), J1.P$12 (GND), J1.P$13 (GND), J8.2, J9.2, JP2.2 (C), PS1.5 (-VO), Q5.2 (S), Q6.2 (S), R7.1, R10.1, R13.2, S1.1, S2.1, TP2.2, U1.1 (GND), U1.15 (GND), U1.38 (GND), U1.39 (GND), U1.40 (GND), U1.41 (GND), U1.42 (GND), U1.43 (GND), U1.44 (GND), U1.45 (GND), U1.46 (GND), U1.47 (GND), U2.3 (V-), U2.15 (GND), U3.1 (GND), U4.1 (GND), U5.3 (GND), U5.29 (GND), U6.2 (GND), U6.3 (CTL)
unnamed: C13.2, JP1.2 (B), Q5.1 (G), Q6.1 (G), R12.2, R13.1
unnamed: C16.1, PS1.3 (+V(CAP))
unnamed: C16.2, C20.1, PS1.4 (-V(CAP))
unnamed: C17.1, L2.1, PS1.6 (+VO)
unnamed: D3.2 (A), R17.2
unnamed: D4.2 (A), R18.2
unnamed: D5.2 (A), R19.2
unnamed: F1.2, R15.1, R16.1
unnamed: L1.1, R15.2
unnamed: L1.2, PS1.2 (AC(L))
unnamed: Q2.2 (B), R4.2
unnamed: Q3.2 (B), R6.2
unnamed: Q4.1 (G), U6.5 (GATE)
unnamed: R3.1, U5.9 (~RST)
unnamed: R7.2, U5.11 (~SUSPEND)
unnamed: R5.2, R10.2, U5.8 (VBUS)

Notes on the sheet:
Powerpath
Reset
USB and Circuitry
Connectors
LEDs
Boot
Thermocouples and Multiplexer
Test Points
NC by Default
Followed Reference Schematic From https://oshwlab.com/robertferanec/esp32-tutorial
ANTENNA
ESP32 MAIN
AC/DC

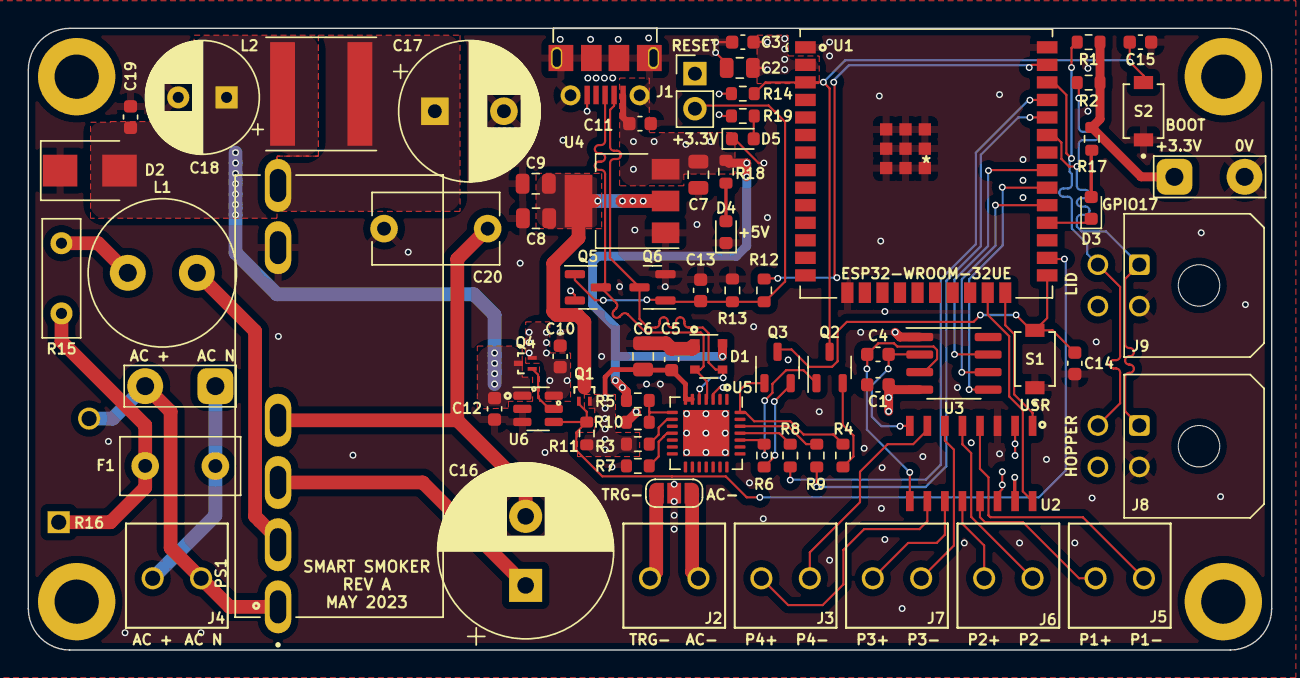
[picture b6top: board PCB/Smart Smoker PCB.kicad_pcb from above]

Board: 4 copper layers, 90.0 x 45.0 mm, 80 parts (1 on the bottom side), 55 nets.
